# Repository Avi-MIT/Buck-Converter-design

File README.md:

There are 3 parts in this project centered around designing a buck converter.
The DESIGN FILES having the schematic and pcb layout files designed in KiCad
The BOM and the design calcualtions files created using wps spreadsheet.

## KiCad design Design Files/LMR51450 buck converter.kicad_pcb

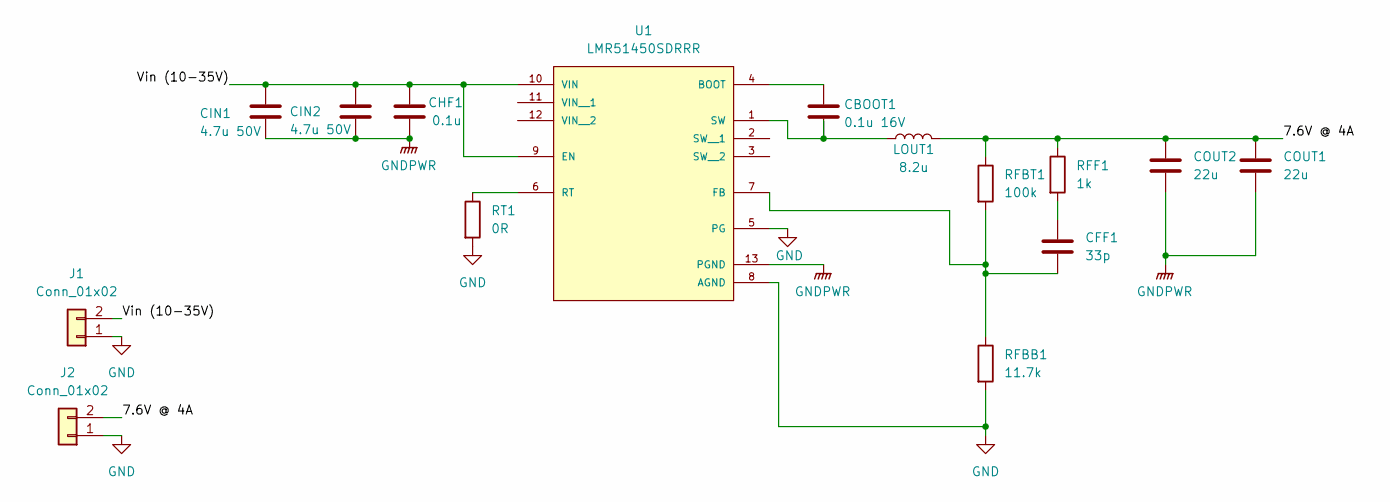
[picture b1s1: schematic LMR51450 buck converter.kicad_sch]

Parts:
CBOOT1: 0.1u 16V; C_01005_0402Metric_Pad0.57x0.30mm_HandSolder
CFF1: 33p; C_0201_0603Metric_Pad0.64x0.40mm_HandSolder
CHF1: 0.1u; C_01005_0402Metric_Pad0.57x0.30mm_HandSolder
CIN1, CIN2: 4.7u 50V; C_1206_3216Metric_Pad1.33x1.80mm_HandSolder
COUT1, COUT2: 22u; C_0805_2012Metric_Pad1.18x1.45mm_HandSolder
J1, J2: Conn_01x02; PinHeader_1x02_P2.54mm_Vertical
LOUT1: 8.2u; L_Bourns_SRP1038C_10.0x10.0mm
RFBB1: 11.7k; R_01005_0402Metric_Pad0.57x0.30mm_HandSolder
RFBT1: 100k; R_01005_0402Metric_Pad0.57x0.30mm_HandSolder
RFF1: 1k; R_01005_0402Metric_Pad0.57x0.30mm_HandSolder
RT1: 0R; R_01005_0402Metric_Pad0.57x0.30mm_HandSolder
U1: LMR51450SDRRR; CONV_LMR51450SDRRR; PARTREV December 2022

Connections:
/7.6V @ 4A: COUT1.1, COUT2.1, J2.2, LOUT1.2, RFBT1.1, RFF1.1
/Vin (10-35V): CHF1.1, CIN1.1, CIN2.1, J1.2, U1.9 (EN), U1.10 (VIN)
GND: J1.1, J2.1, RFBB1.2, RT1.2, U1.5 (PG), U1.8 (AGND)
GNDPWR: CHF1.2, CIN1.2, CIN2.2, COUT1.2, COUT2.2, U1.13 (PGND)
unnamed: CFF1.1, RFF1.2
unnamed: CBOOT1.1, U1.4 (BOOT)
unnamed: CFF1.2, RFBB1.1, RFBT1.2, U1.7 (FB)
unnamed: RT1.1, U1.6 (RT)
unnamed: CBOOT1.2, LOUT1.1, U1.1 (SW)

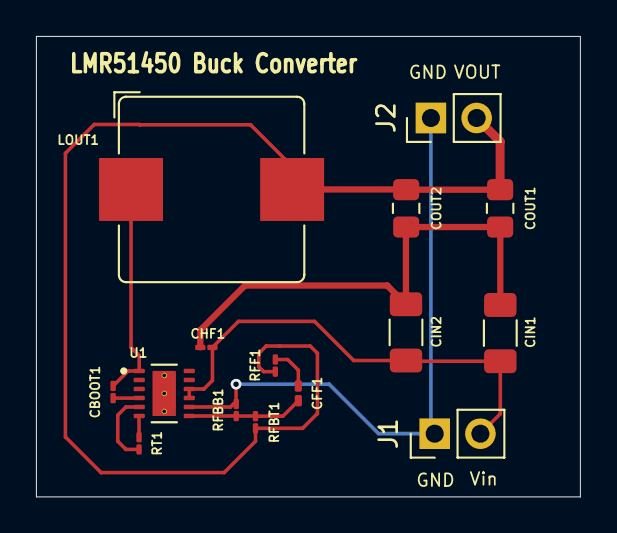
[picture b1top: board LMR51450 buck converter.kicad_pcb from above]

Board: 2 copper layers, 30.2 x 25.6 mm, 15 parts (0 on the bottom side), 9 nets.

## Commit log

2025-09-14 Design Files/placeholder.txt
